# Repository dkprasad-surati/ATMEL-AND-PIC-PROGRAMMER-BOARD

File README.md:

# ATMEL-AND-PIC-PROGRAMMER-BOARD
ALL IN ONE PROGRAMMER BOARD PORTABLE ORDER (PROTEUS OR GERBER FILE)

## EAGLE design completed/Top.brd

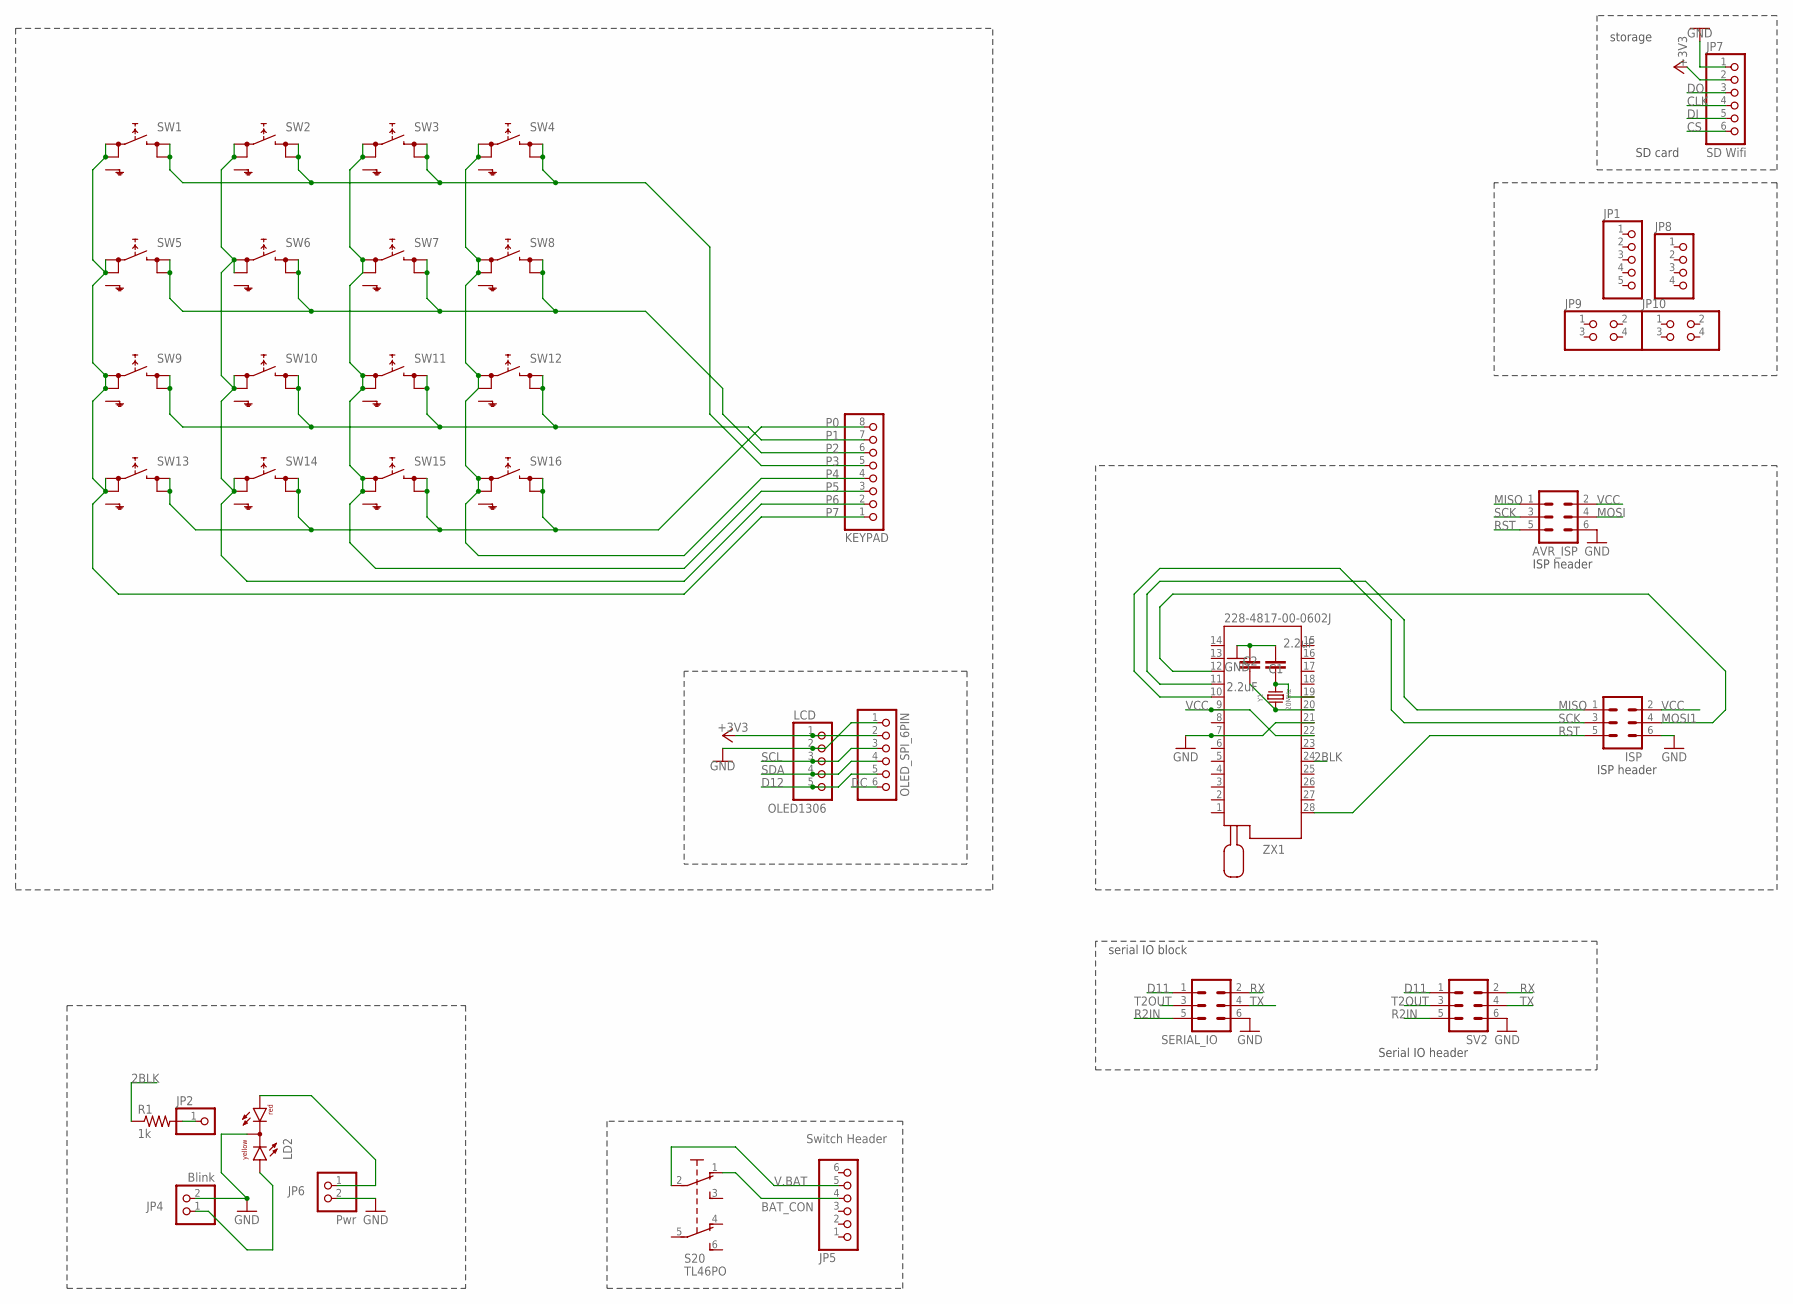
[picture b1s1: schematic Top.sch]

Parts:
AVR_ISP: ML6
C1, C2: 2.2uF; 1206
ISP: ML6
JP1: PINHD-1X5; 1X05
JP2: PINHD-1X1; 1X01
JP4: Blink; 1X02
JP5: Switch Header; 1X06
JP6: Pwr; 1X02
JP7: SD Wifi; 1X06
JP8: PINHD-1X4; 1X04
JP9, JP10: PINHD-2X2; 2X02
KEYPAD: PINHD-1X8; 1X08
LCD: OLED1306; 1X05
LD2: DUOLED-RY-C; DUOLED-C-5MM
OLED_SPI_6PIN: PINHD-1X6; 1X06
R1: 1k; M1206
S20: TL46PO; TL4XPO
SERIAL_IO: ML6
SV2: ML6
SW1, SW2, SW3, SW4, SW5, SW6, SW7, SW8, SW9, SW10, SW11, SW12, SW13, SW14, SW15, SW16: SKHMPSE010; SKHMPXE010
Y1: 20MHz; WE-XTAL_HC49/4HSMX
ZX1: 228-4817-00-0602J

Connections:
2BLK: R1.1, ZX1.24
+3V3: JP7.2, LCD.1, OLED_SPI_6PIN.2
BAT_CON: JP5.4, S20.1 (O)
CLK: JP7.4
CS: JP7.6
D11: SERIAL_IO.1, SV2.1
D12: LCD.5, OLED_SPI_6PIN.5
DC: OLED_SPI_6PIN.6
DI: JP7.5
DO: JP7.3
GND: AVR_ISP.6, C1.2, C2.1, ISP.6, JP4.2, JP6.2, JP7.1, LCD.2, LD2.C, OLED_SPI_6PIN.1, SERIAL_IO.6, SV2.6, ZX1.7, ZX1.21
MISO: AVR_ISP.1, ISP.1, ZX1.11
MOSI: AVR_ISP.4
MOSI1: ISP.4, ZX1.12
unnamed: C1.1, Y1.2, ZX1.19
unnamed: C2.2, Y1.1, ZX1.20
unnamed: JP6.1, LD2.AR
unnamed: JP2.1, R1.2
unnamed: JP4.1, LD2.AX (AY)
P0: KEYPAD.8, SW13.3 (2.1), SW13.4 (2.2), SW14.3 (2.1), SW14.4 (2.2), SW15.3 (2.1), SW15.4 (2.2), SW16.3 (2.1), SW16.4 (2.2)
P1: KEYPAD.7, SW9.3 (2.1), SW9.4 (2.2), SW10.3 (2.1), SW10.4 (2.2), SW11.3 (2.1), SW11.4 (2.2), SW12.3 (2.1), SW12.4 (2.2)
P2: KEYPAD.6, SW5.3 (2.1), SW5.4 (2.2), SW6.3 (2.1), SW6.4 (2.2), SW7.3 (2.1), SW7.4 (2.2), SW8.3 (2.1), SW8.4 (2.2)
P3: KEYPAD.5, SW1.3 (2.1), SW1.4 (2.2), SW2.3 (2.1), SW2.4 (2.2), SW3.3 (2.1), SW3.4 (2.2), SW4.3 (2.1), SW4.4 (2.2)
P4: KEYPAD.4, SW4.1 (1.1), SW4.2 (1.2), SW8.1 (1.1), SW8.2 (1.2), SW12.1 (1.1), SW12.2 (1.2), SW16.1 (1.1), SW16.2 (1.2)
P5: KEYPAD.3, SW3.1 (1.1), SW3.2 (1.2), SW7.1 (1.1), SW7.2 (1.2), SW11.1 (1.1), SW11.2 (1.2), SW15.1 (1.1), SW15.2 (1.2)
P6: KEYPAD.2, SW2.1 (1.1), SW2.2 (1.2), SW6.1 (1.1), SW6.2 (1.2), SW10.1 (1.1), SW10.2 (1.2), SW14.1 (1.1), SW14.2 (1.2)
P7: KEYPAD.1, SW1.1 (1.1), SW1.2 (1.2), SW5.1 (1.1), SW5.2 (1.2), SW9.1 (1.1), SW9.2 (1.2), SW13.1 (1.1), SW13.2 (1.2)
R2IN: SERIAL_IO.5, SV2.5
RST: AVR_ISP.5, ISP.5, ZX1.28
RX: SERIAL_IO.2, SV2.2
SCK: AVR_ISP.3, ISP.3, ZX1.10
SCL: LCD.3, OLED_SPI_6PIN.3
SDA: LCD.4, OLED_SPI_6PIN.4
T2OUT: SERIAL_IO.3, SV2.3
TX: SERIAL_IO.4, SV2.4
V.BAT: JP5.5, S20.2
VCC: AVR_ISP.2, ISP.2, ZX1.9, ZX1.22

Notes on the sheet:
ISP header
Serial IO header
SD card
serial IO block
storage

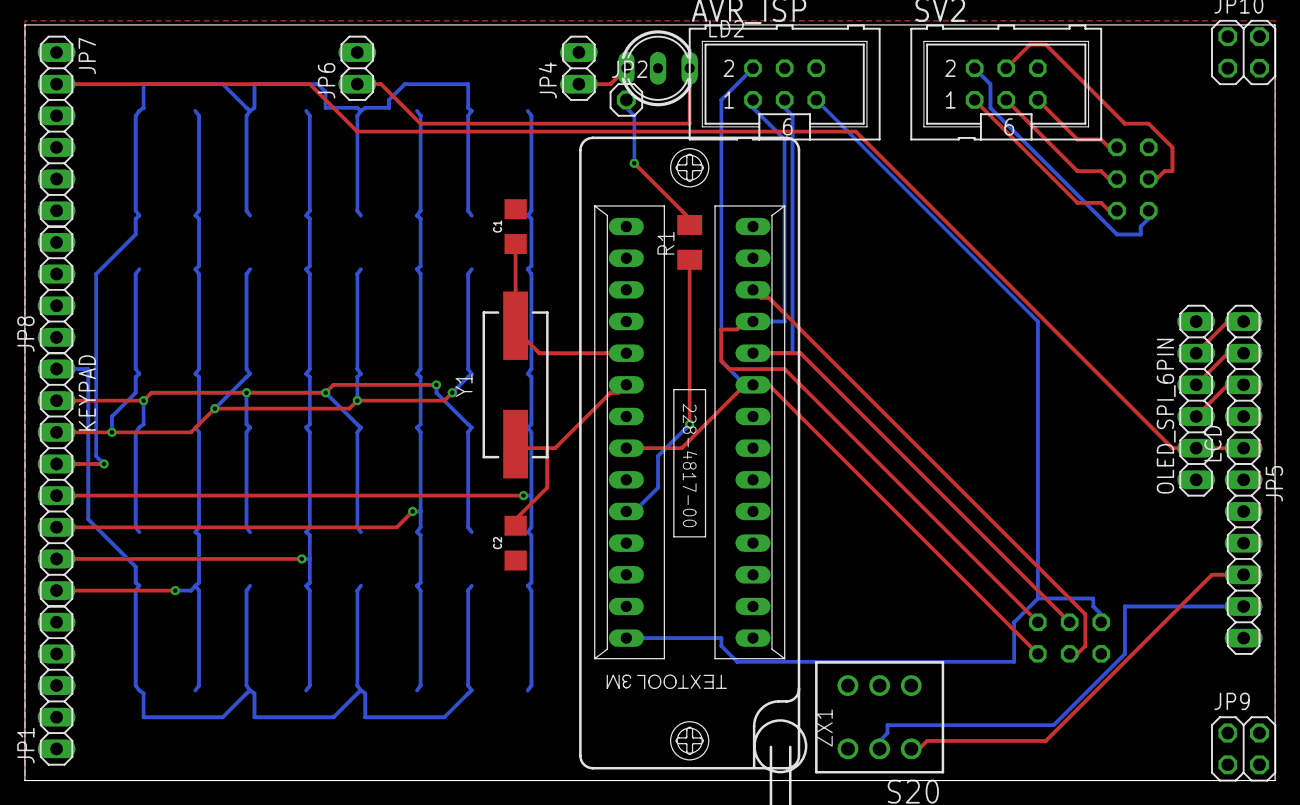
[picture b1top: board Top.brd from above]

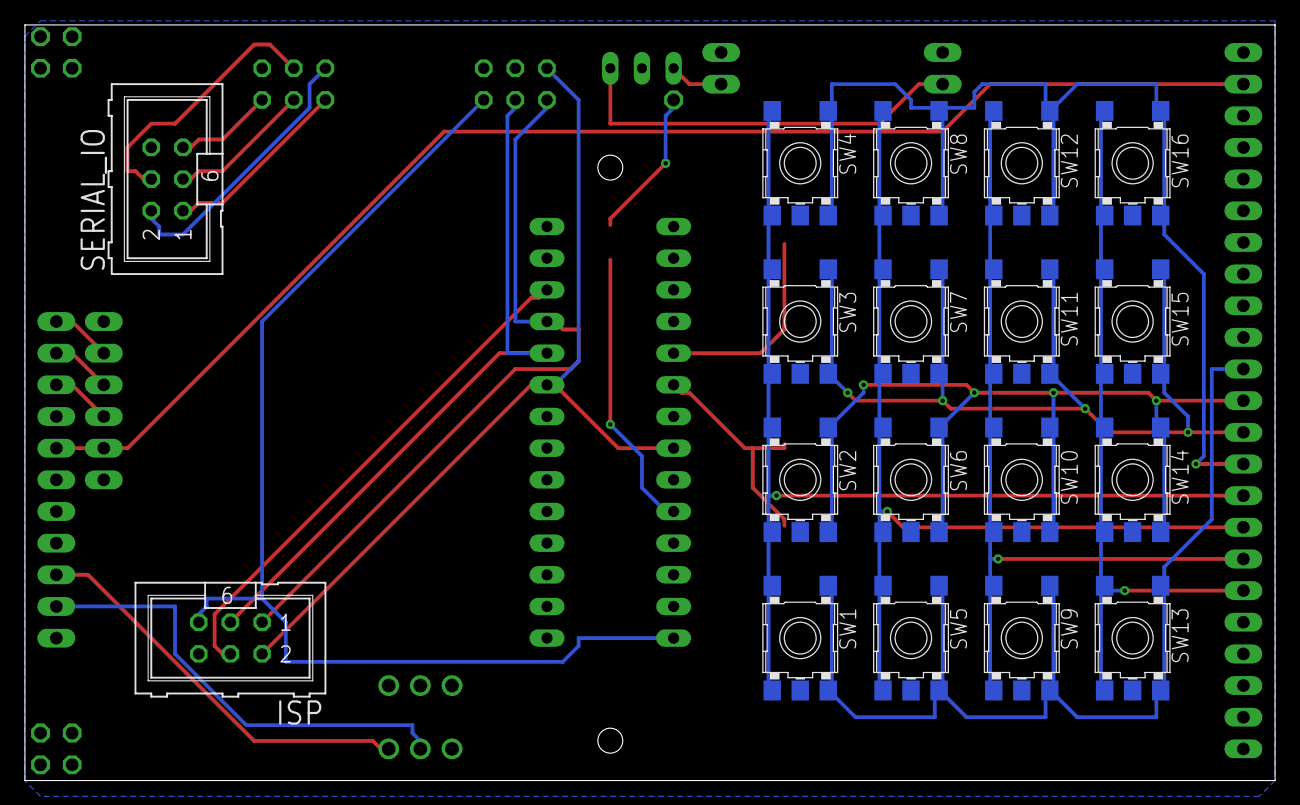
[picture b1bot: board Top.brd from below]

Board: 2 copper layers, 100.3 x 60.6 mm, 39 parts (18 on the bottom side), 31 nets.

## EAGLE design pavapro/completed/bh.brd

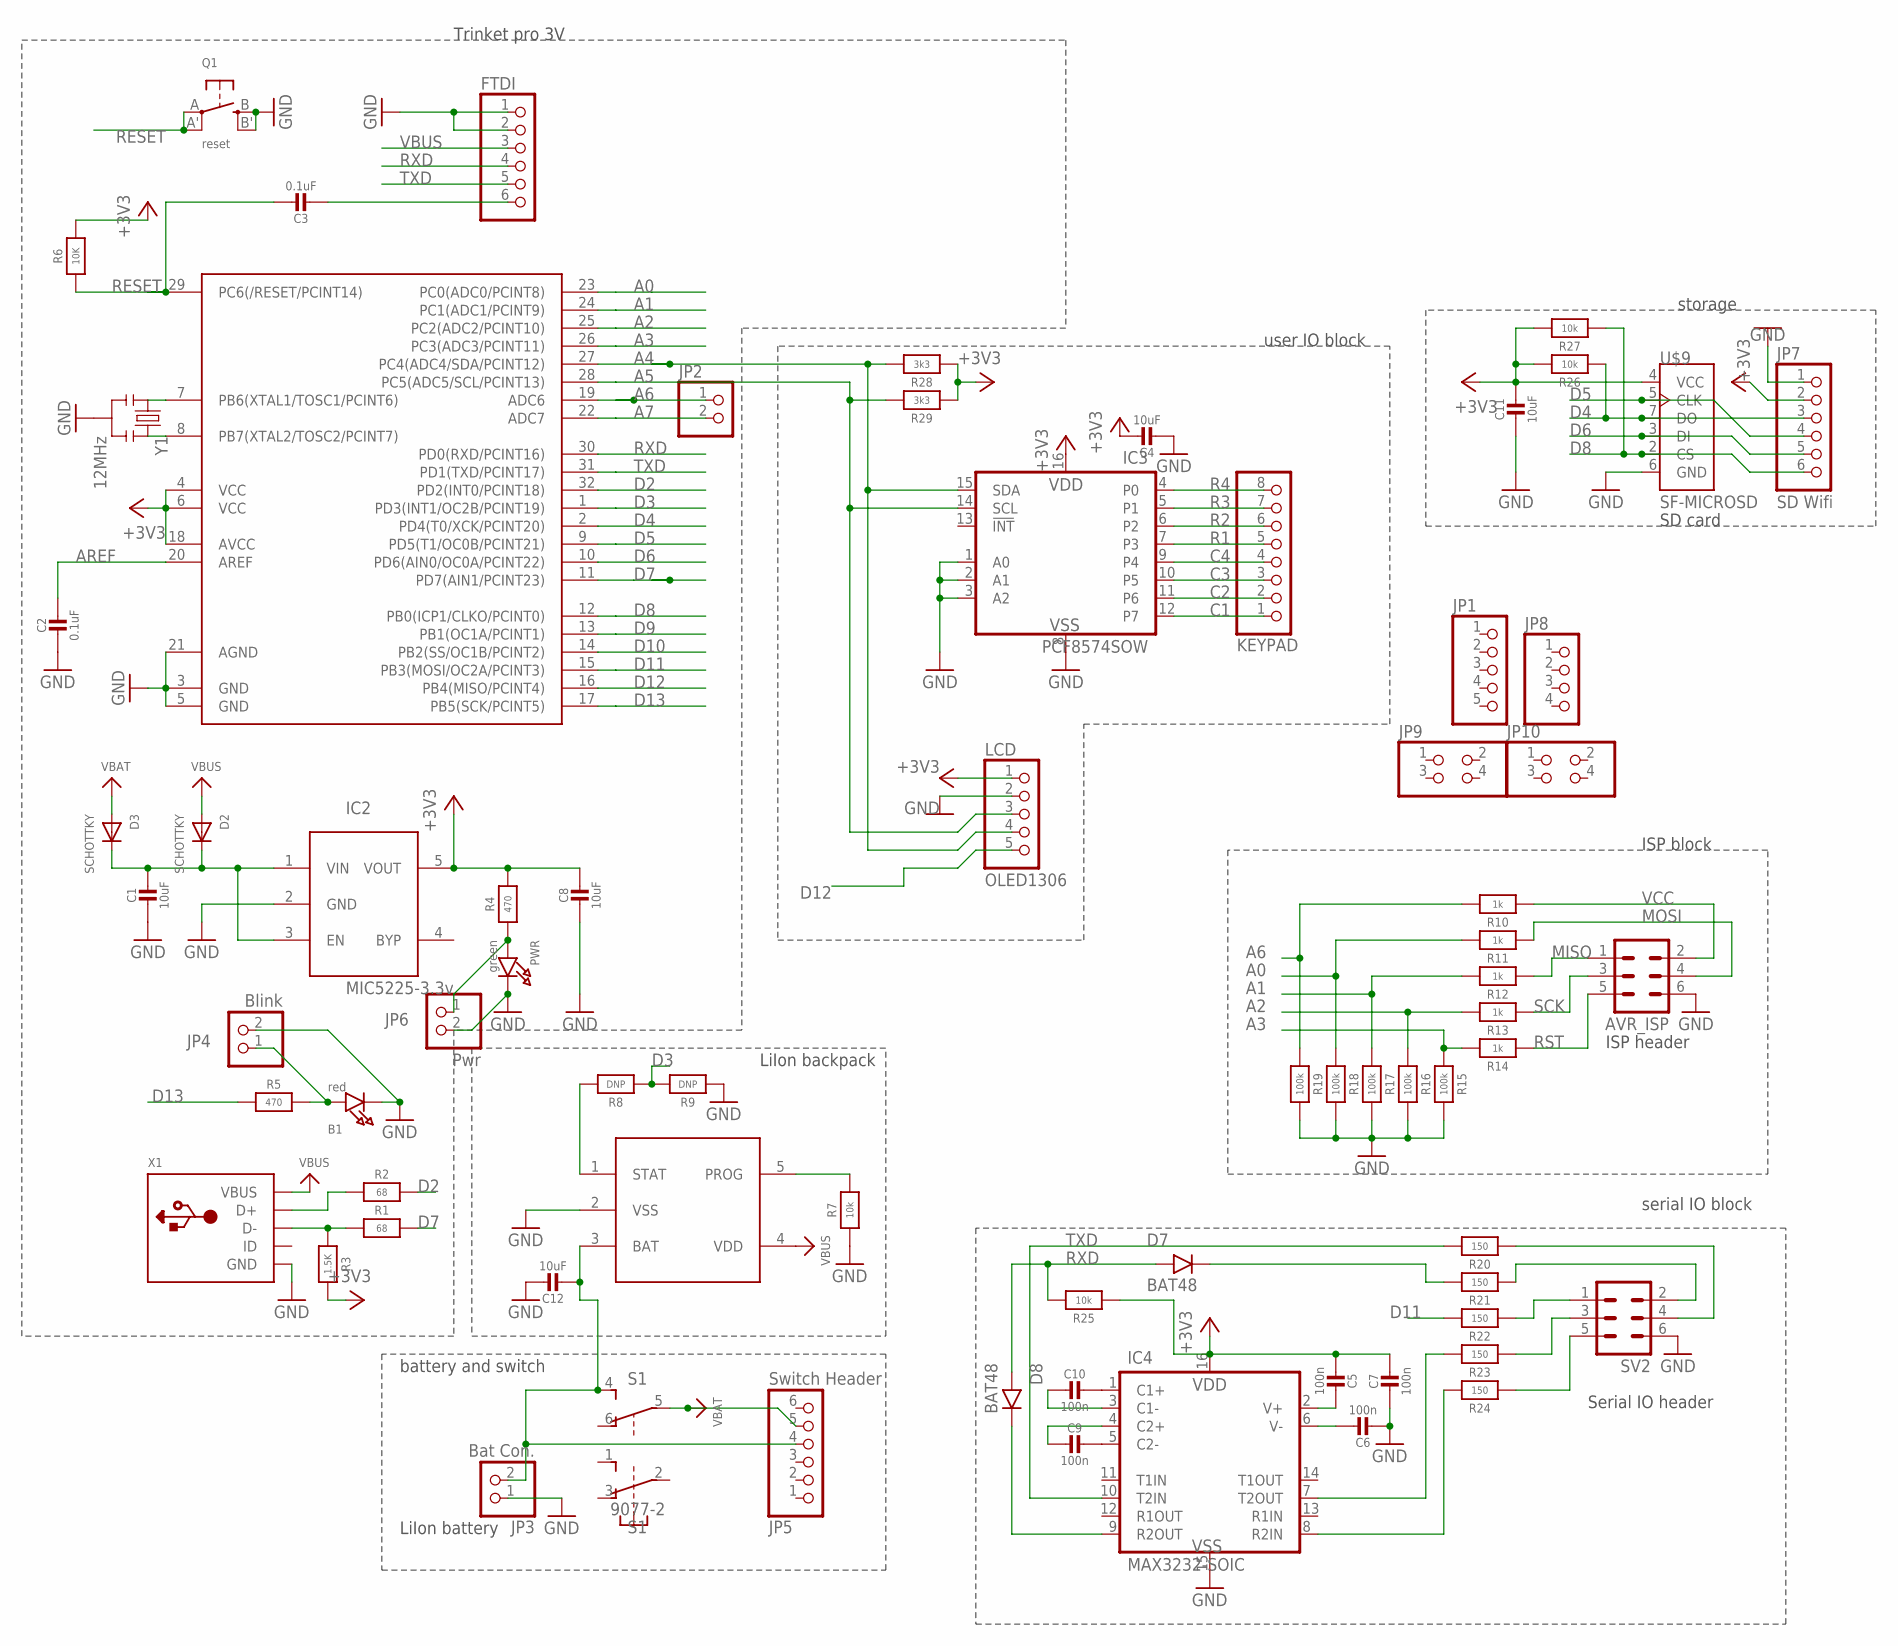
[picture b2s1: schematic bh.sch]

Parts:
AVR_ISP: ML6
B1: red; CHIPLED_0805_NOOUTLINE
C1, C4, C8, C11, C12: 10uF; 0805-NO
C2: 0.1uF; _0805MP
C3: 0.1uF; 0805-NO
C5, C6, C7, C9, C10: 100n; 0805-NO
D2, D3: SCHOTTKY; ADAFRUIT_SOD-123FL
D7, D8: BAT48; SOD-80
FTDI: ADAFRUIT_PINHD-1X6CB; ADAFRUIT_1X06-CLEANBIG
IC2: MIC5225-3.3v; SOT23-5L
IC3: PCF8574SOW; SO-16DW
IC4: MAX3232-SOIC; SO-16
IC5: MEGA328P; TQFP32-08
JP1: PINHD-1X5; 1X05
JP2: HEADER-1X2ROUND; 1X02_ROUND
JP3: Bat Con.; 1X02/90
JP4: Blink; 1X02
JP5: Switch Header; 1X06
JP6: Pwr; 1X02
JP7: SD Wifi; 1X06
JP8: PINHD-1X4; 1X04
JP9, JP10: PINHD-2X2; 2X02
KEYPAD: PINHD-1X8; 1X08
LCD: OLED1306; 1X05
PWR: green; CHIPLED_0805_NOOUTLINE
Q1: reset; BTN_KMR2_4.6X2.8
R1, R2: 68; 0603-NO
R3: 1.5K; 0603-NO
R4, R5: 470; 0603-NO
R6: 10K; 0805-NO
R7, R25, R26, R27: 10k; _0805
R8, R9: DNP; _0805
R10, R11, R12, R13, R14: 1k; _0805
R15, R16, R17, R18, R19: 100k; _0805
R20, R21, R22, R23, R24: 150; _0805
R28, R29: 3k3; _0805
S1: 9077-2
SV2: ML6
U$6: MCP73831; SOT23-5
U$9: SF-MICROSD; MICROSD
X1: MICROBUILDER_USBMICRO_20329; MICROBUILDER_4UCONN_20329
Y1: 12MHz; RESONATOR-SMD

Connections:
+3V3: C4.1, C5.2, C7.1, C8.1, C11.1, IC2.5 (VOUT), IC3.16 (VDD), IC4.16 (VDD), IC5.4 (VCC), IC5.6 (VCC), IC5.18 (AVCC), JP7.2, LCD.1, R3.2, R4.2, R6.2, R25.2, R26.1, R27.1, R28.2, R29.2, U$9.4 (VCC)
A0: IC5.23 (PC0(ADC0/PCINT8)), R11.1, R18.2
A1: IC5.24 (PC1(ADC1/PCINT9)), R12.1, R17.2
A2: IC5.25 (PC2(ADC2/PCINT10)), R13.1, R16.2
A3: IC5.26 (PC3(ADC3/PCINT11)), R14.1, R15.2
A4: IC3.15 (SDA), IC5.27 (PC4(ADC4/SDA/PCINT12)), LCD.4, R28.1
A5: IC3.14 (SCL), IC5.28 (PC5(ADC5/SCL/PCINT13)), LCD.3, R29.1
A6: IC5.19 (ADC6), JP2.1, R10.1, R19.2
A7: IC5.22 (ADC7), JP2.2
AREF: C2.1, IC5.20 (AREF)
C1: IC3.12 (P7), KEYPAD.1
C2: IC3.11 (P6), KEYPAD.2
C3: IC3.10 (P5), KEYPAD.3
C4: IC3.9 (P4), KEYPAD.4
D2: IC5.32 (PD2(INT0/PCINT18)), R2.2
D3: IC5.1 (PD3(INT1/OC2B/PCINT19)), R8.2, R9.1
D4: IC5.2 (PD4(T0/XCK/PCINT20)), JP7.3, R26.2, U$9.7 (DO)
D5: IC5.9 (PD5(T1/OC0B/PCINT21)), JP7.4, U$9.5 (CLK)
D6: IC5.10 (PD6(AIN0/OC0A/PCINT22)), JP7.5, U$9.3 (DI)
D7: IC5.11 (PD7(AIN1/PCINT23)), R1.2
D8: IC5.12 (PB0(ICP1/CLKO/PCINT0)), JP7.6, R27.2, U$9.2 (CS)
D9: IC5.13 (PB1(OC1A/PCINT1))
D10: IC5.14 (PB2(SS/OC1B/PCINT2))
D11: IC5.15 (PB3(MOSI/OC2A/PCINT3)), R22.1
D12: IC5.16 (PB4(MISO/PCINT4)), LCD.5
D13: IC5.17 (PB5(SCK/PCINT5)), R5.2
D+: R2.1, X1.D+
D-: R1.1, R3.1, X1.D-
DTR/RTS: C3.2, FTDI.6
GND: AVR_ISP.6, B1.C, C1.2, C2.2, C4.2, C6.2, C7.2, C8.2, C11.2, C12.1, FTDI.1, FTDI.2, IC2.2 (GND), IC3.1 (A0), IC3.2 (A1), IC3.3 (A2), IC3.8 (VSS), IC4.15 (VSS), IC5.3 (GND), IC5.5 (GND), IC5.21 (AGND), JP3.1, JP4.2, JP6.2, JP7.1, LCD.2, PWR.C, Q1.B (S), Q1.B' (S1), R7.2, R9.2, R15.1, R16.1, R17.1, R18.1, R19.1, SV2.6, U$6.2 (VSS), U$9.6 (GND), X1.BASE@1 (GND), X1.BASE@2 (GND), X1.GND, X1.SPRT@1 (GND), X1.SPRT@2 (GND), X1.SPRT@3 (GND), X1.SPRT@4 (GND), Y1.2
MISO: AVR_ISP.1, R12.2
MOSI: AVR_ISP.4, R11.2
unnamed: IC5.7 (PB6(XTAL1/TOSC1/PCINT6)), Y1.1
unnamed: IC5.8 (PB7(XTAL2/TOSC2/PCINT7)), Y1.3
unnamed: JP6.1, PWR.A, R4.1
unnamed: C1.1, D2.C, D3.C, IC2.1 (VIN), IC2.3 (EN)
unnamed: B1.A, JP4.1, R5.1
unnamed: C12.2, JP3.2, JP5.4, S1.4 (S), U$6.3 (BAT)
unnamed: R7.1, U$6.5 (PROG)
unnamed: R8.1, U$6.1 (STAT)
unnamed: R20.2, SV2.4
unnamed: R21.2, SV2.2
unnamed: R22.2, SV2.1
unnamed: R23.2, SV2.3
unnamed: R24.2, SV2.5
unnamed: IC4.7 (T2OUT), R23.1
unnamed: D7.K, R21.1
unnamed: D8.K, IC4.9 (R2OUT)
unnamed: C6.1, IC4.6 (V-)
unnamed: C5.1, IC4.2 (V+)
unnamed: C9.1, IC4.5 (C2-)
unnamed: C10.1, IC4.1 (C1+)
unnamed: C10.2, IC4.3 (C1-)
unnamed: C9.2, IC4.4 (C2+)
unnamed: IC4.8 (R2IN), R24.1
R1: IC3.7 (P3), KEYPAD.5
R2: IC3.6 (P2), KEYPAD.6
R3: IC3.5 (P1), KEYPAD.7
R4: IC3.4 (P0), KEYPAD.8
RESET: C3.1, IC5.29 (PC6(/RESET/PCINT14)), Q1.A, Q1.A' (P1), R6.1
RST: AVR_ISP.5, R14.2
RXD: D7.A, D8.A, FTDI.4, IC5.30 (PD0(RXD/PCINT16)), R25.1
SCK: AVR_ISP.3, R13.2
TXD: FTDI.5, IC4.10 (T2IN), IC5.31 (PD1(TXD/PCINT17)), R20.1
VBAT: D3.A, JP5.5, S1.5
VBUS: D2.A, FTDI.3, U$6.4 (VDD), X1.VBUS
VCC: AVR_ISP.2, R10.2

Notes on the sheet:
Trinket pro 3V
LiIon backpack
LiIon battery
ISP header
Serial IO header
SD card
serial IO block
ISP block
user IO block
storage
battery and switch

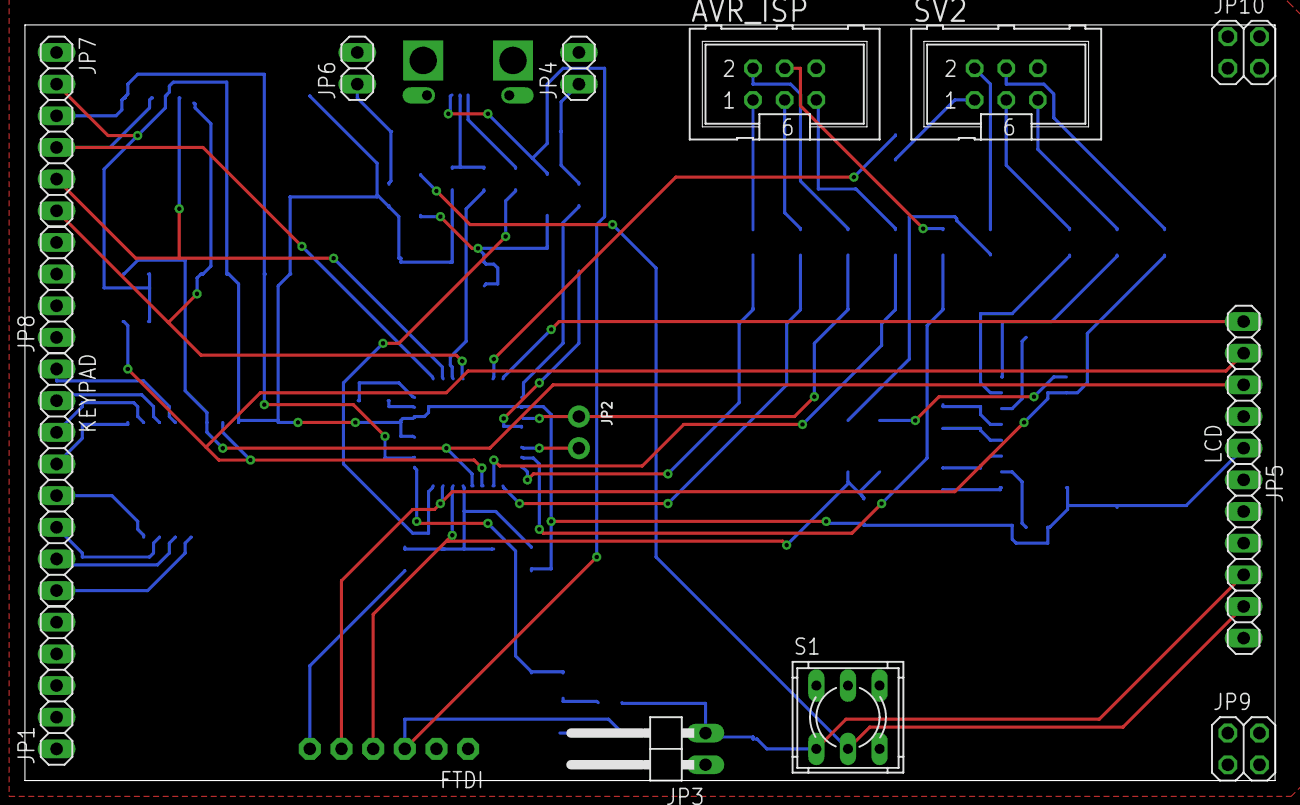
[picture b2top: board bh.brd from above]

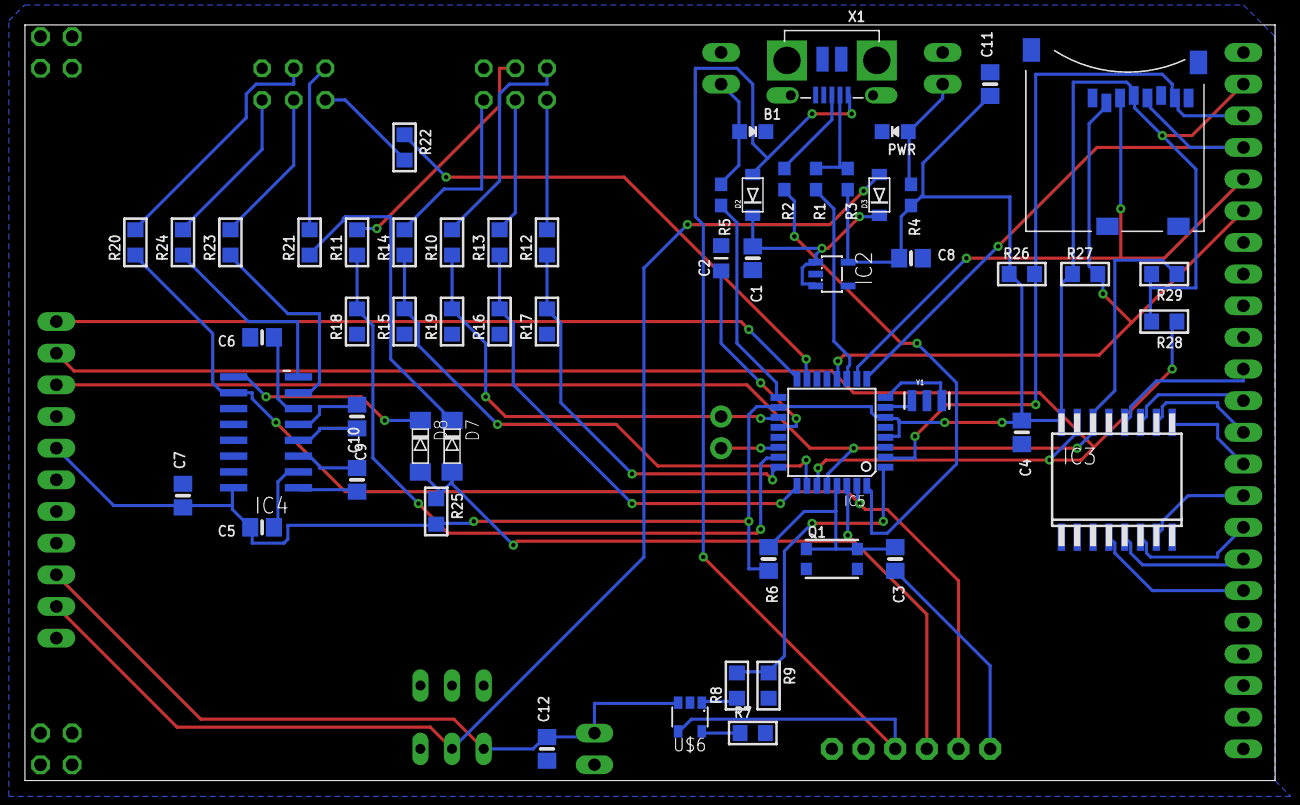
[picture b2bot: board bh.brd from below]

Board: 2 copper layers, 100.3 x 60.6 mm, 72 parts (56 on the bottom side), 65 nets.

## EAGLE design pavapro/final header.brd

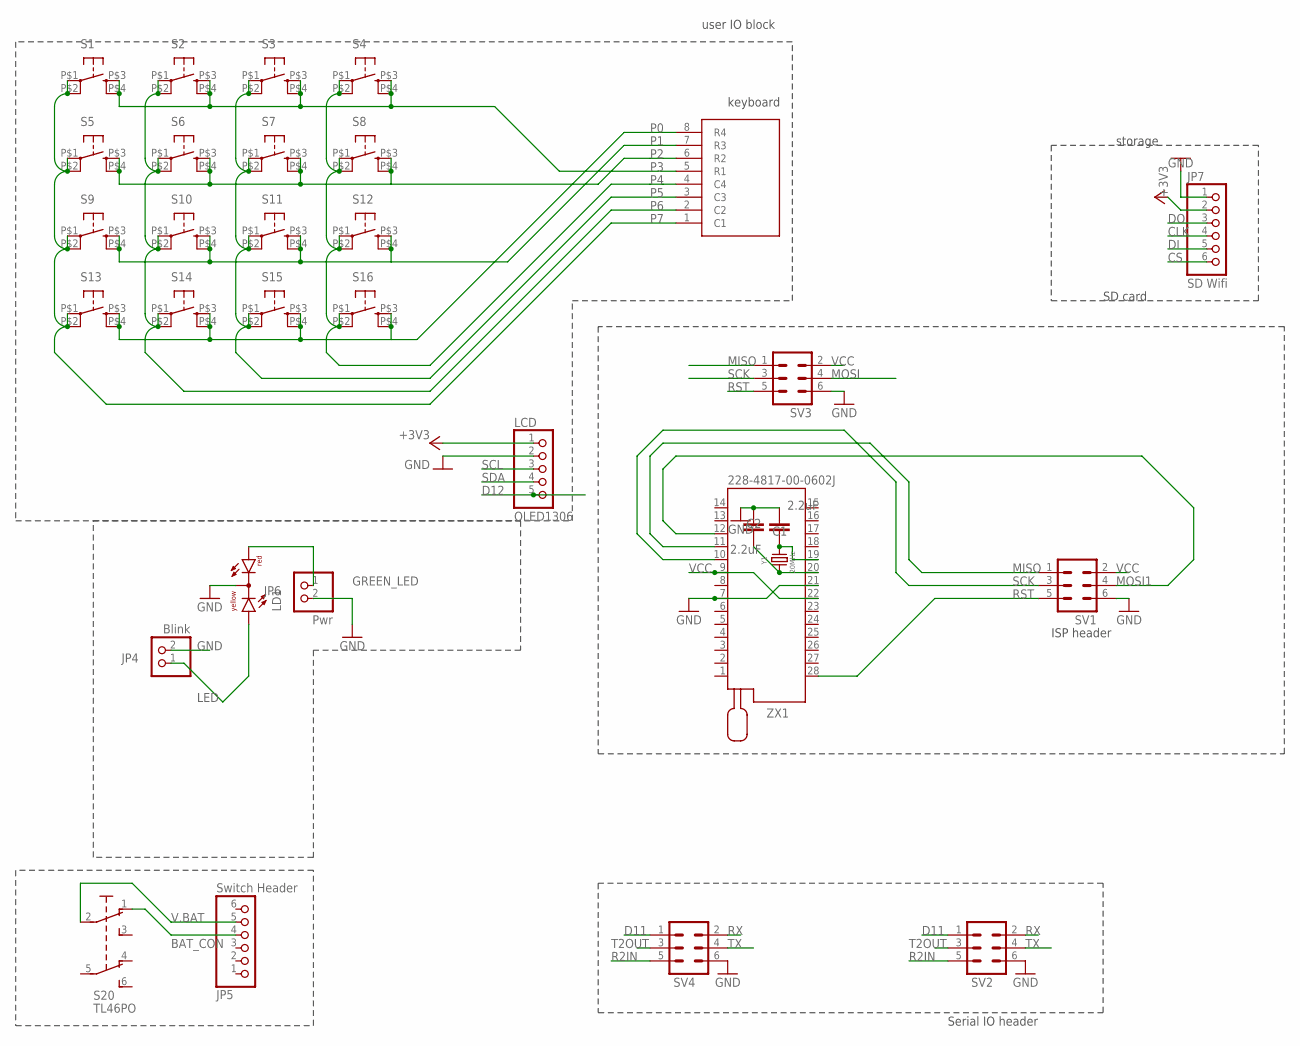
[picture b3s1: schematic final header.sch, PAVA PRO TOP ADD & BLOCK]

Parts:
C1, C2: 2.2uF; 1206
JP4: Blink; 1X02
JP5: Switch Header; 1X06
JP6: Pwr; 1X02
JP7: SD Wifi; 1X06
LCD: OLED1306; 1X05
LD1: DUOLED-RY-C; DUOLED-C-5MM
S1, S2, S3, S4, S5, S6, S7, S8, S9, S10, S11, S12, S13, S14, S15, S16: 10-XX-SMD; B3F-10XX-SMD
S20: TL46PO; TL4XPO
SV1, SV2, SV3, SV4: ML6
U$7: KB1604
Y1: 20MHz; WE-XTAL_HC49/4HSMX
ZX1: 228-4817-00-0602J

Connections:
+3V3: JP7.2, LCD.1
BAT_CON: JP5.4, S20.1 (O)
CLK: JP7.4
CS: JP7.6
D11: SV2.1, SV4.1
D12: LCD.5
DI: JP7.5
DO: JP7.3
GND: C1.2, C2.1, JP4.2, JP6.2, JP7.1, LCD.2, LD1.C, SV1.6, SV2.6, SV3.6, SV4.6, ZX1.7, ZX1.21
GREEN_LED: JP6.1, LD1.AR
LED: JP4.1, LD1.AX (AY)
MISO: SV1.1, SV3.1, ZX1.11
MOSI: SV3.4
MOSI1: SV1.4, ZX1.12
unnamed: C2.2, Y1.1, ZX1.20
unnamed: C1.1, Y1.2, ZX1.19
unnamed: S9.P$3 (S), S9.P$4 (S1), S10.P$3 (S), S10.P$4 (S1), S11.P$3 (S), S11.P$4 (S1), S12.P$3 (S), S12.P$4 (S1)
P0: S13.P$3 (S), S13.P$4 (S1), S14.P$3 (S), S14.P$4 (S1), S15.P$3 (S), S15.P$4 (S1), S16.P$3 (S), S16.P$4 (S1), U$7.8 (R4)
P1: U$7.7 (R3)
P2: S5.P$3 (S), S5.P$4 (S1), S6.P$3 (S), S6.P$4 (S1), S7.P$3 (S), S7.P$4 (S1), S8.P$3 (S), S8.P$4 (S1), U$7.6 (R2)
P3: S1.P$3 (S), S1.P$4 (S1), S2.P$3 (S), S2.P$4 (S1), S3.P$3 (S), S3.P$4 (S1), S4.P$3 (S), S4.P$4 (S1), U$7.5 (R1)
P4: S4.P$1, S4.P$2 (P1), S8.P$1, S8.P$2 (P1), S12.P$1, S12.P$2 (P1), S16.P$1, S16.P$2 (P1), U$7.4 (C4)
P5: S3.P$1, S3.P$2 (P1), S7.P$1, S7.P$2 (P1), S11.P$1, S11.P$2 (P1), S15.P$1, S15.P$2 (P1), U$7.3 (C3)
P6: S2.P$1, S2.P$2 (P1), S6.P$1, S6.P$2 (P1), S10.P$1, S10.P$2 (P1), S14.P$1, S14.P$2 (P1), U$7.2 (C2)
P7: S1.P$1, S1.P$2 (P1), S5.P$1, S5.P$2 (P1), S9.P$1, S9.P$2 (P1), S13.P$1, S13.P$2 (P1), U$7.1 (C1)
R2IN: SV2.5, SV4.5
RST: SV1.5, SV3.5, ZX1.28
RX: SV2.2, SV4.2
SCK: SV1.3, SV3.3, ZX1.10
SCL: LCD.3
SDA: LCD.4
T2OUT: SV2.3, SV4.3
TX: SV2.4, SV4.4
V.BAT: JP5.5, S20.2
VCC: SV1.2, SV3.2, ZX1.9, ZX1.22

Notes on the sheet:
ISP header
Serial IO header
SD card
keyboard
user IO block
storage

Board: 2 copper layers, 32 parts (17 on the bottom side), 26 nets, no tracks yet.

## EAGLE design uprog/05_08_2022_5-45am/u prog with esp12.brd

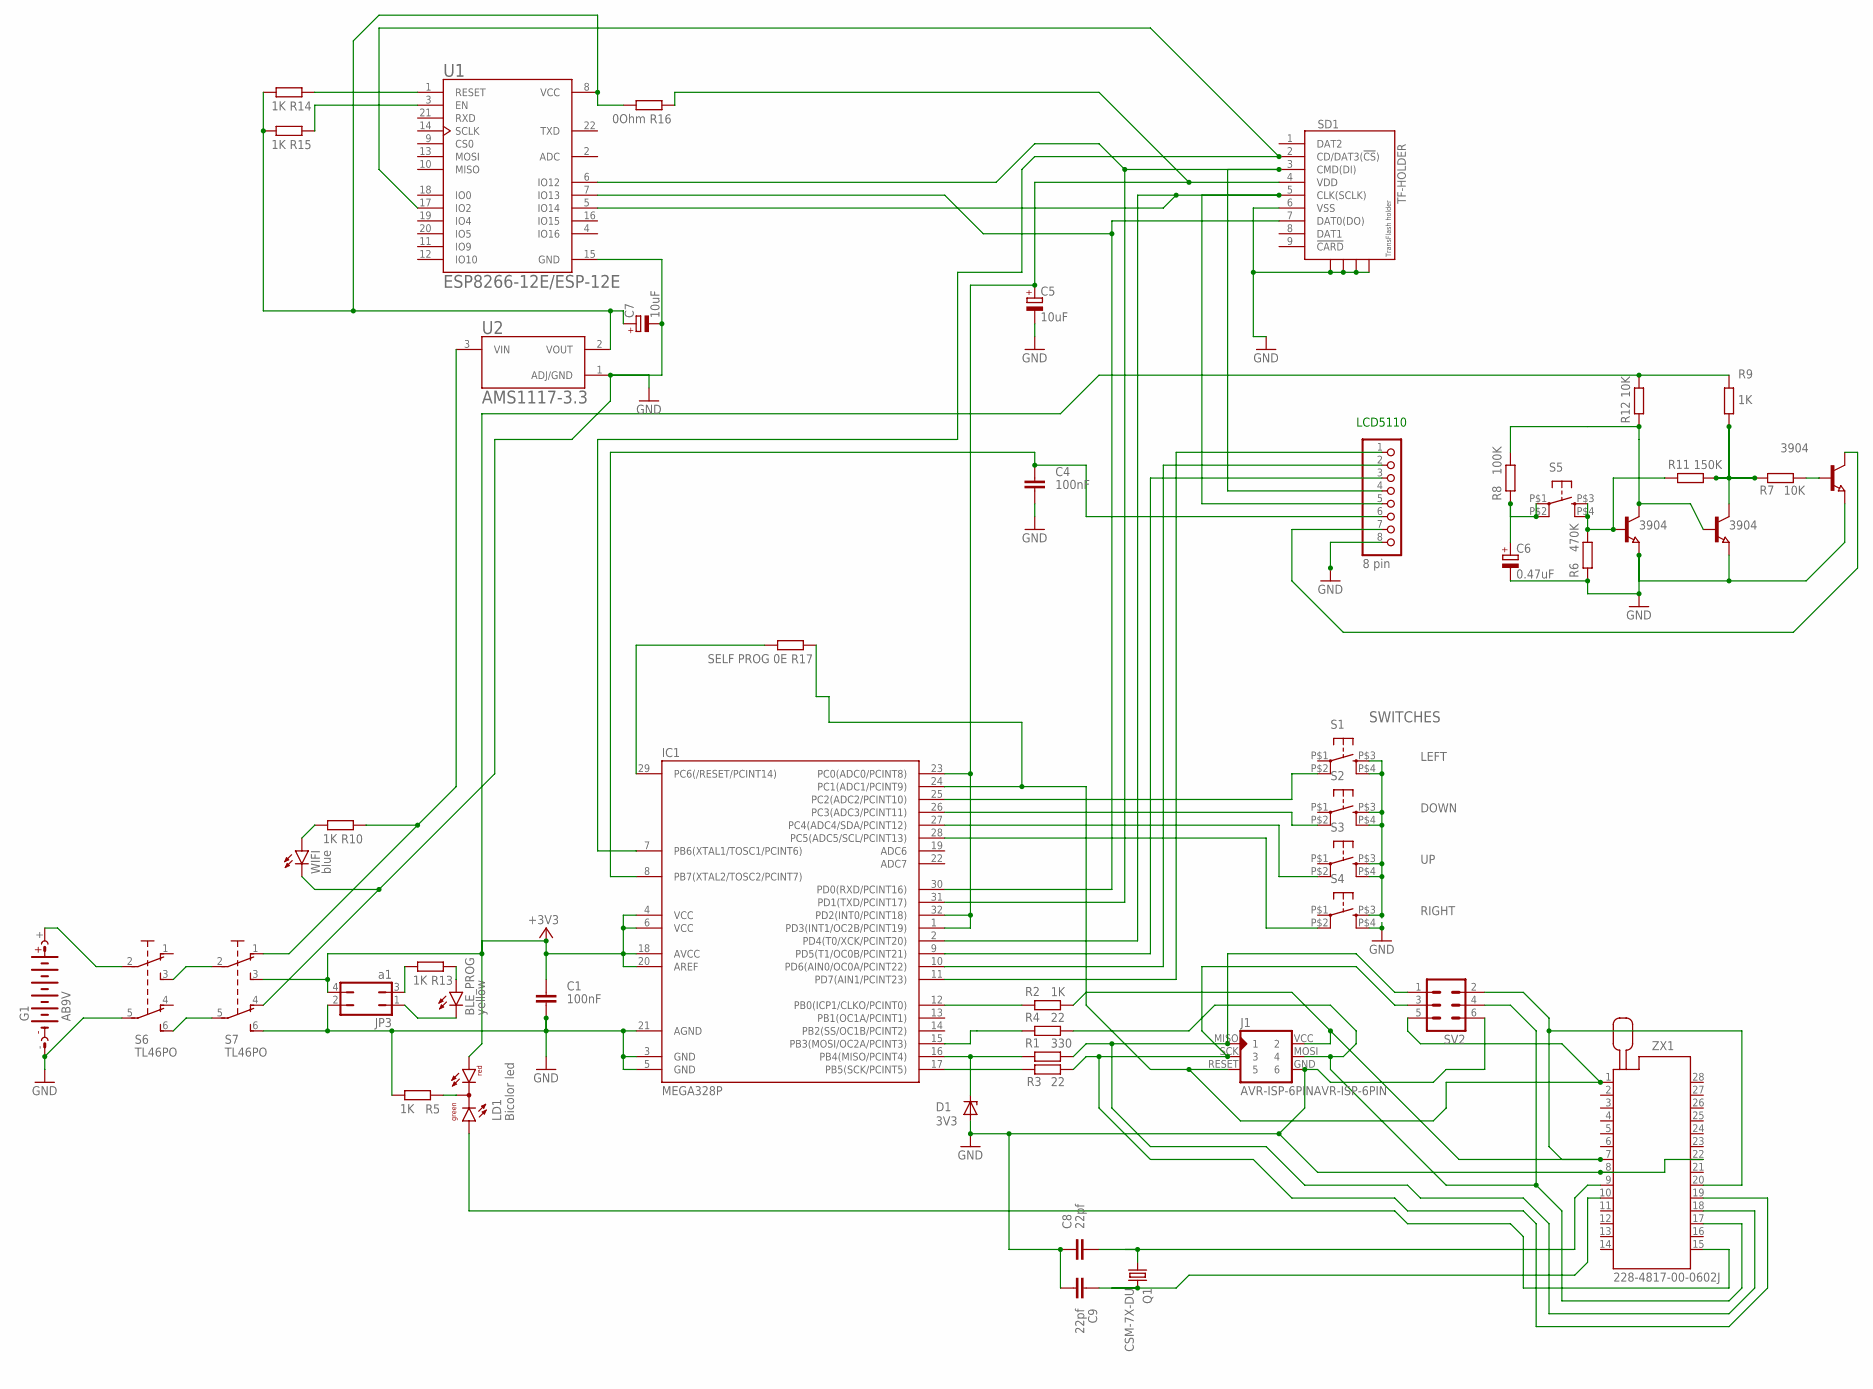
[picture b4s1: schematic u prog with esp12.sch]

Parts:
BLE_PROG: yellow; LED5MM
C1, C4: 100nF; C0805
C5, C7: 10uF; C/6032-28R
C6: 0.47uF; C/6032-28R
C8, C9: 22pf; C0805
D1: 3V3; SOD80C
G1: AB9V
IC1: MEGA328P; TQFP32-08
J1: AVR-ISP-6PINAVR-ISP-6PIN; AVR-ISP-6PIN
JP1: 8 pin; 1X08
JP3: a1; JP2Q
LD1: Bicolor led; DUOLED-C-5MM
Q1: CSM-7X-DU
Q2, Q3, Q4: 3904; SOT23
R1: 330; R0805
R2, R5, R9, R10, R13, R14, R15: 1K; R0805
R3, R4: 22; R0805
R6: 470K; R0805
R7, R12: 10K; R0805
R8: 100K; R0805
R11: 150K; R0805
R16: 0Ohm; R0805
R17: SELF PROG 0E; R0805
S1, S2, S3, S4, S5: 10-XX-SMD; B3F-10XX-SMD
S6, S7: TL46PO; TL4XPO
SD1: TF-HOLDER; TF-PULL
SV2: MA03-2
U1: ESP8266-12E/ESP-12E; XCVR_ESP8266-12E/ESP-12E
U2: AMS1117-3.3; SOT229P700X180-4N
WIFI: blue; LED5MM
ZX1: 228-4817-00-0602J

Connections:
+3V3: C1.1, IC1.4 (VCC), IC1.6 (VCC), IC1.18 (AVCC), IC1.20 (AREF), JP3.4, LD1.AR, R9.1, R12.2, S7.3 (S)
GND: C1.2, C4.2, C5.-, C6.-, C7.-, C8.1, C9.2, D1.A, G1.-, IC1.3 (GND), IC1.5 (GND), IC1.21 (AGND), J1.GND (6), JP1.8, JP3.2, Q2.2 (E), Q3.2 (E), Q4.2 (E), R5.2, R6.1, S1.P$3 (S), S1.P$4 (S1), S2.P$3 (S), S2.P$4 (S1), S3.P$3 (S), S3.P$4 (S1), S4.P$3 (S), S4.P$4 (S1), S6.5 (P1), S7.4 (O1), S7.6 (S1), SD1.6 (VSS), SD1.S1, SD1.S2, SD1.S3, SD1.S4, SV2.6, U1.15 (GND), U2.1 (ADJ/GND), WIFI.K (C), ZX1.8, ZX1.22
LCD-VCC: C4.1, IC1.8 (PB7(XTAL2/TOSC2/PCINT7)), JP1.6
MOSI: IC1.15 (PB3(MOSI/OC2A/PCINT3)), R4.1
unnamed: IC1.17 (PB5(SCK/PCINT5)), R3.1
unnamed: IC1.12 (PB0(ICP1/CLKO/PCINT0)), R2.1
unnamed: D1.C, IC1.16 (PB4(MISO/PCINT4)), R1.1
unnamed: IC1.9 (PD5(T1/OC0B/PCINT21)), JP1.3
unnamed: J1.MISO (1), R1.2, SV2.1, ZX1.18
unnamed: J1.SCK (3), R3.2, SV2.3, ZX1.19
unnamed: LD1.C, R5.1
unnamed: G1.+, S6.2
unnamed: IC1.30 (PD0(RXD/PCINT16)), SD1.7 (DAT0(DO)), U1.7 (IO13)
unnamed: C8.2, Q1.1, ZX1.9
unnamed: IC1.11 (PD7(AIN1/PCINT23)), JP1.1
unnamed: IC1.10 (PD6(AIN0/OC0A/PCINT22)), JP1.2
unnamed: IC1.31 (PD1(TXD/PCINT17)), JP1.4, SD1.3 (CMD(DI)), U1.6 (IO12)
unnamed: C9.1, Q1.2, ZX1.10
unnamed: Q2.3 (C), Q3.1 (B), R8.2, R12.1
unnamed: Q3.3 (C), R7.1, R9.2, R11.2
unnamed: IC1.29 (PC6(/RESET/PCINT14)), R17.2
unnamed: J1.VCC (2), R2.2, SV2.2, ZX1.7, ZX1.20
unnamed: Q2.1 (B), R6.2, R11.1, S5.P$3 (S), S5.P$4 (S1)
unnamed: J1.MOSI (4), R4.2, SV2.4, ZX1.17
unnamed: IC1.28 (PC5(ADC5/SCL/PCINT13)), S4.P$2 (P1)
unnamed: IC1.27 (PC4(ADC4/SDA/PCINT12)), S3.P$2 (P1)
unnamed: IC1.26 (PC3(ADC3/PCINT11)), S2.P$2 (P1)
unnamed: IC1.25 (PC2(ADC2/PCINT10)), S1.P$2 (P1)
unnamed: LD1.AX (AG), ZX1.15
unnamed: C6.+, R8.1, S5.P$1, S5.P$2 (P1)
unnamed: Q4.1 (B), R7.2
unnamed: JP1.7, Q4.3 (C)
unnamed: IC1.7 (PB6(XTAL1/TOSC1/PCINT6)), SD1.2 (CD/DAT3(!CS!)), U1.17 (IO2)
unnamed: BLE_PROG.A, R13.1
unnamed: S6.6 (S1), S7.5 (P1)
unnamed: S6.3 (S), S7.2
unnamed: R10.2, WIFI.A
unnamed: R10.1, S7.1 (O), U2.3 (VIN)
unnamed: BLE_PROG.K (C), JP3.1
unnamed: JP3.3, R13.2
unnamed: R14.1, U1.1 (RESET)
unnamed: R15.1, U1.3 (EN)
unnamed: C7.+, R14.2, R15.2, R16.2, U1.8 (VCC), U2.2 (VOUT)
RST: IC1.24 (PC1(ADC1/PCINT9)), J1.RESET (5), R17.1, SV2.5, ZX1.1
SCK2: IC1.2 (PD4(T0/XCK/PCINT20)), JP1.5, SD1.5 (CLK(SCLK)), U1.5 (IO14)
SD-VCC: C5.+, IC1.1 (PD3(INT1/OC2B/PCINT19)), IC1.23 (PC0(ADC0/PCINT8)), IC1.32 (PD2(INT0/PCINT18)), R16.1, SD1.4 (VDD)

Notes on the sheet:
LEFT
DOWN
RIGHT
SWITCHES
LCD5110

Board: 2 copper layers, 49 parts (22 on the bottom side), 46 nets, no tracks yet.

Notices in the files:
parts and their libraries:
SparkFun-Capacitors: Licensing: Creative Commons ShareAlike 4.0 International - https://creativecommons.org/licenses/by-sa/4.0
Wurth_Quartz Crystals: Copyright: Würth Elektronik
SparkFun: Licensing: CC v3.0 Share-Alike You are welcome to use this library for commercial purposes.
